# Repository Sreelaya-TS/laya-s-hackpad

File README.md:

# 🖱️ Laya’s Hackpad (Custom Macropad)

A custom-built **4-key macropad** designed for coding shortcuts, powered by **Seeed Studio XIAO RP2040**, with a fully 3D-printed case and KMK firmware.
honestly this was my first ever hardware project where i used the pcb editon and fusion 360 it was fun i had to google a lot of things and i tried to draw doreamon on back of my 
case it didnt extract well although i was succesfull in drawing a small robo on my pcb anyways i will continue working and learning abt it more this project taught me a lot than my traditional education could ever do

---

## 📸 Project Images

| Preview | Description |
|------|------------|
|  | Macropad – top view |
|  | Macropad – bottom view |
| ) | Custom PCB layout |
|  | schemantic (`code.py`) |

> 📌 Images are stored in the `IMAGES/` folder.

---

## 🧩 Bill of Materials (BOM)

### Required Components

| Qty | Component | Notes |
|---|---|---|
| 1 | Seeed Studio XIAO RP2040 | Main microcontroller |
| 4 | Mechanical key switches | MX-compatible |
| 4 | Keycaps | Any MX keycaps |
| 1 | Custom PCB | Designed for XIAO RP2040 |
| 1 | USB-C cable | Programming & power |
| 1 | 3D-printed case | Top & bottom enclosure |

---

## ⌨️ Firmware

- Firmware is written using **KMK**
- File location: `Firmware/code.py`
- Board: **Seeed Studio XIAO RP2040**
- Supports custom macros for coding shortcuts

---

## 🔌 Default Key Mapping

| Key | Function |
|---|---|
| 1 | Save (Ctrl + S) |
| 2 | Screenshot (Win + Shift + S) |
| 3 | Shutdown (Ctrl + Alt + Del) |
| 4 | Print (Ctrl + P) |

---

## 🛠️ Tools Used

- KiCad (PCB design)
- KMK Firmware
- Fusion 360 / CAD software
- 3D Printer
- Git & GitHub

---

## 📄 License

This project is open-source and intended for educational and personal use.

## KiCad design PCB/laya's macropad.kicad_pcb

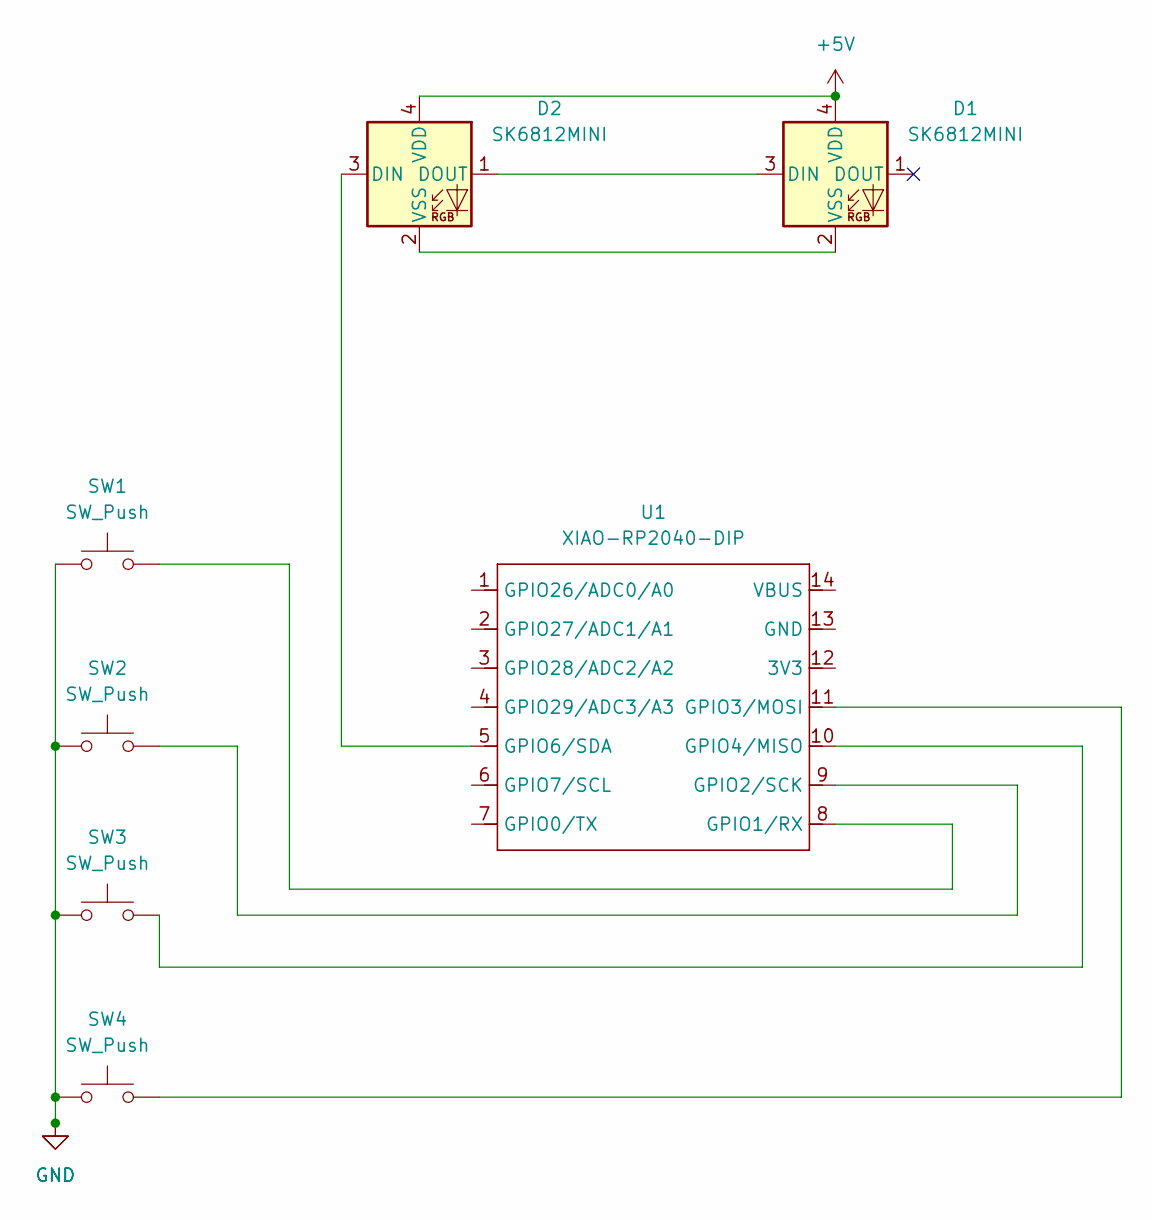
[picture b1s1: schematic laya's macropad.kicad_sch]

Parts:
D1, D2: SK6812MINI; LED_SK6812MINI_PLCC4_3.5x3.5mm_P1.75mm
SW1, SW2, SW3, SW4: SW_Push; SW_Cherry_MX_1.00u_PCB
U1: XIAO-RP2040-DIP

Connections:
+5V: D1.4 (VDD), D2.4 (VDD)
GND: SW1.1, SW2.1, SW3.1, SW4.1
unnamed: D1.3 (DIN), D2.1 (DOUT)
unnamed: D1.2 (VSS), D2.2 (VSS)
unnamed: D2.3 (DIN), U1.5 (GPIO6/SDA)
unnamed: SW1.2, U1.8 (GPIO1/RX)
unnamed: SW2.2, U1.9 (GPIO2/SCK)
unnamed: SW4.2, U1.11 (GPIO3/MOSI)
unnamed: SW3.2, U1.10 (GPIO4/MISO)

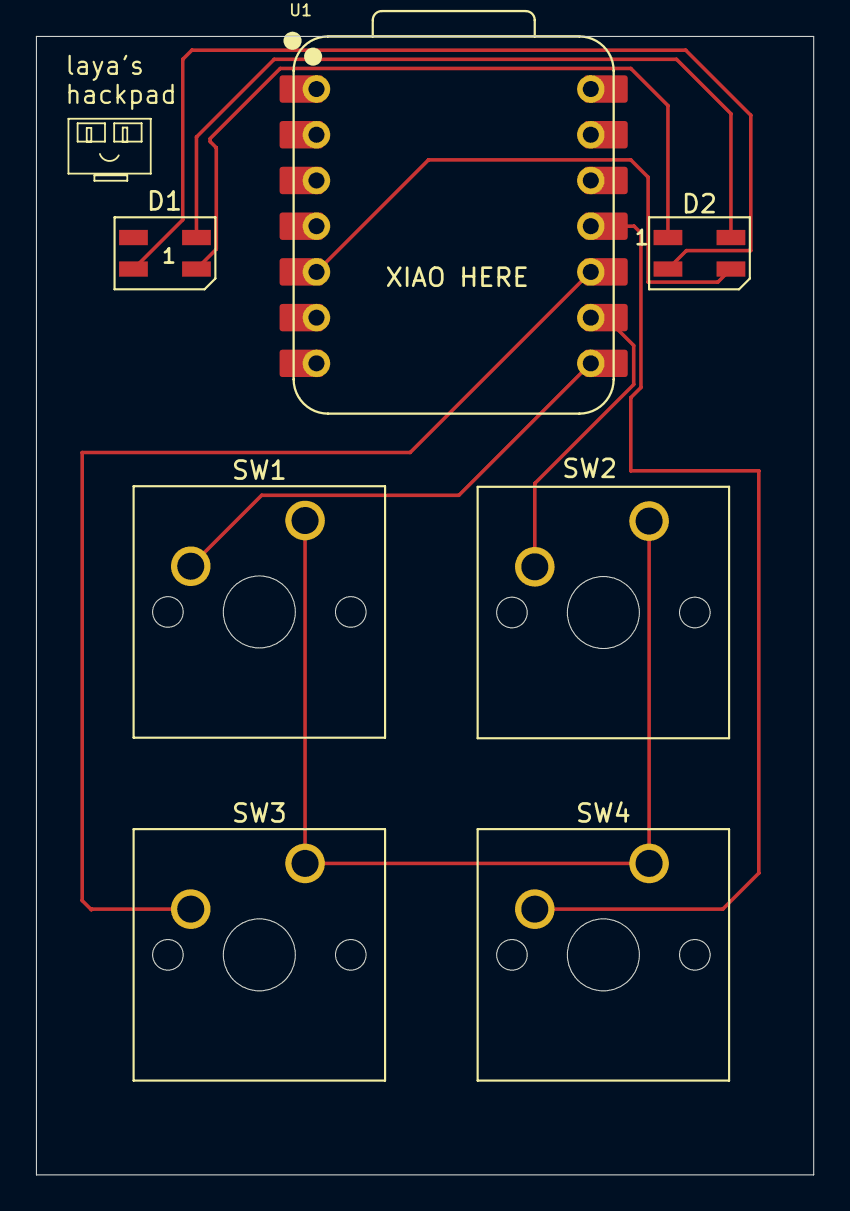
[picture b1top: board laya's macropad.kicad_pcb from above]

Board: 2 copper layers, 43.2 x 63.2 mm, 7 parts (0 on the bottom side), 9 nets.

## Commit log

2026-02-04 Initial macropad files
2026-02-04 Add project screenshot
2026-02-04 added top and bottom views
2026-02-04 Initialize README with project details and resources
    Added detailed project description, images, BOM, firmware information, key mapping, tools used, and license.
